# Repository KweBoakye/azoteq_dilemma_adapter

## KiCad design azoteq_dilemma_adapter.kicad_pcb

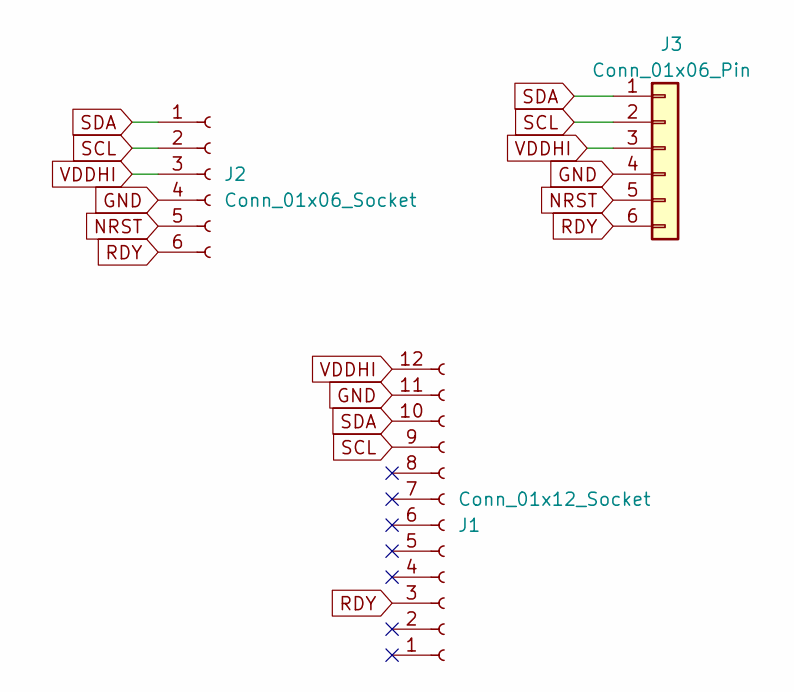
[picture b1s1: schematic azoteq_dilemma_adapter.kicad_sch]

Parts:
J1: Conn_01x12_Socket; Hirose_FH12-12S-0.5SH_1x12-1MP_P0.50mm_Horizontal
J2: Conn_01x06_Socket; Hirose_FH12-6S-0.5SH_1x06-1MP_P0.50mm_Horizontal
J3: Conn_01x06_Pin; PinSocket_1x06_P2.54mm_Vertical

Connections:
GND: J1.11, J2.4, J3.4
NRST: J2.5, J3.5
RDY: J1.3, J2.6, J3.6
SCL: J1.9, J2.2, J3.2
SDA: J1.10, J2.1, J3.1
VDDHI: J1.12, J2.3, J3.3

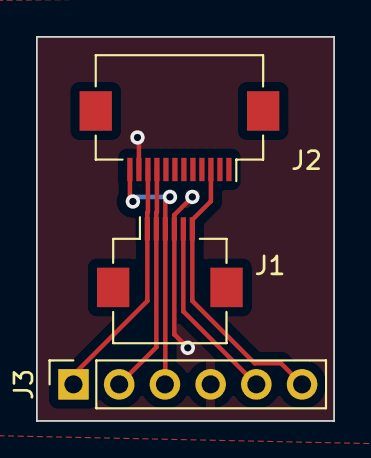
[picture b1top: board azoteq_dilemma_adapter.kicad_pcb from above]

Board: 2 copper layers, 16.5 x 21.3 mm, 3 parts (0 on the bottom side), 6 nets.

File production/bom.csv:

Designator,Footprint,Quantity,Value,LCSC Part #
J1,Hirose_FH12-12S-0.5SH_1x12-1MP_P0.50mm_Horizontal,1,Conn_01x12_Socket,
J2,Hirose_FH12-6S-0.5SH_1x06-1MP_P0.50mm_Horizontal,1,Conn_01x06_Socket,
J3,PinSocket_1x06_P2.54mm_Vertical,1,Conn_01x06_Pin,

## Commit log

2024-05-01 initial commit, pcb ready to be made and tested
